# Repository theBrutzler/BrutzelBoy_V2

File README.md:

https://github.com/jsc69/theLittleBrutzelboy/releases/tag/0.8a
link to the brutzleboy game

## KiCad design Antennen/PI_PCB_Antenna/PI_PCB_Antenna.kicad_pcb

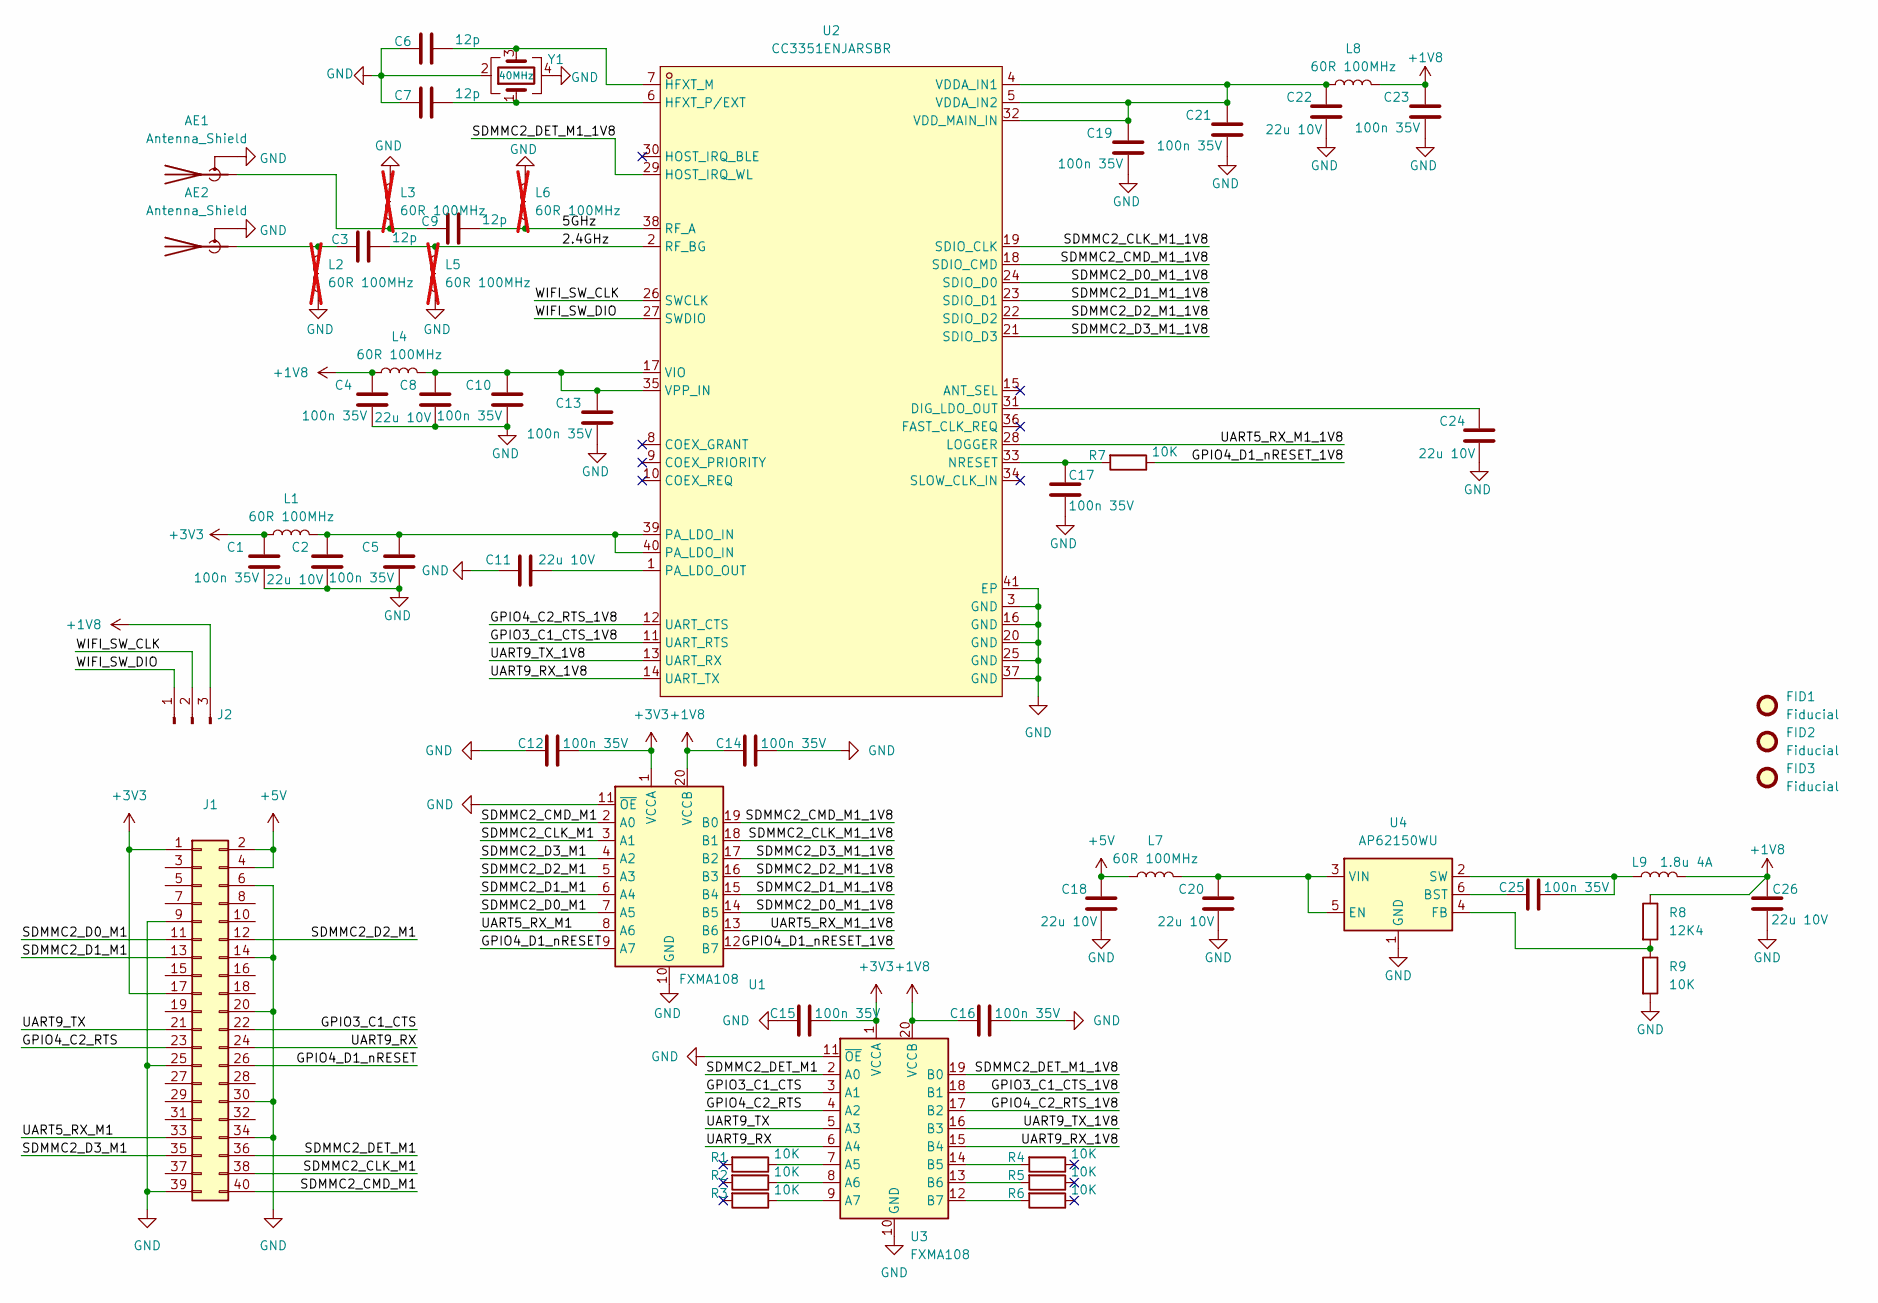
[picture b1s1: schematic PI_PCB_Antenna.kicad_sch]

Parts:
AE1, AE2: Antenna_Shield; PI_Antenne
C1, C4, C5, C10, C12, C13, C14, C15, C16, C17, C19, C21, C23, C25: 100n 35V; C_0603_1608Metric; LCSC C48579281
C2, C8, C11, C18, C20, C22, C24, C26: 22u 10V; C_0603_1608Metric; LCSC C7432770
C3, C6, C7, C9: 12p; C_0603_1608Metric; LCSC C45359931
FID1, FID2, FID3: Fiducial; Fiducial_0.5mm_Mask1mm
J1: Conn_02x20_Odd_Even; PinHeader_2x20_P2.54mm_Vertical
J2: Conn_01x03_Pin; PinHeader_1x03_P2.54mm_Vertical
L1, L4, L7, L8: 60R 100MHz; L_0603_1608Metric; LCSC C356980
L2, L3, L5, L6: 60R 100MHz; L_0603_1608Metric; LCSC C356980; not fitted
L9: 1.8u 4A; L_1008_2520Metric; LCSC C53285288
R1, R2, R3, R4, R5, R6, R7, R9: 10K; R_0603_1608Metric
R8: 12K4; R_0603_1608Metric
U1, U3: FXMA108; WQFN-20-1EP_2.5x4.5mm_P0.5mm_EP1x2.9mm
U2: CC3351ENJARSBR; WQFN-40_L5.0-W5.0-P0.40-TL-EP3.5; LCSC Part C41671458
U4: AP62150WU; TSOT-23-6; LCSC C3194237
Y1: 40MHz; Oscillator_SMD_ECS_2520MV-xxx-xx-4Pin_2.5x2.0mm; LCSC C337601

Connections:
+1V8: C4.1, C14.1, C16.1, C23.1, C26.2, J2.3, L4.1, L8.2, L9.2, R8.1, U1.20 (VCCB), U3.20 (VCCB)
+3V3: C1.1, C12.2, C15.2, J1.1, J1.17, L1.1, U1.1 (VCCA), U3.1 (VCCA)
+5V: C18.2, J1.2, J1.4, L7.1
/2.4GHz: C3.2, L5.2, U2.2 (RF_BG)
/5GHz: C9.2, L6.1, U2.38 (RF_A)
/GPIO3_C1_CTS: J1.22, U3.3 (A1)
/GPIO3_C1_CTS_1V8: U2.11 (UART_RTS), U3.18 (B1)
/GPIO4_C2_RTS: J1.23, U3.4 (A2)
/GPIO4_C2_RTS_1V8: U2.12 (UART_CTS), U3.17 (B2)
/GPIO4_D1_nRESET: J1.26, U1.9 (A7)
/GPIO4_D1_nRESET_1V8: R7.1, U1.12 (B7)
/SDMMC2_CLK_M1: J1.38, U1.3 (A1)
/SDMMC2_CLK_M1_1V8: U1.18 (B1), U2.19 (SDIO_CLK)
/SDMMC2_CMD_M1: J1.40, U1.2 (A0)
/SDMMC2_CMD_M1_1V8: U1.19 (B0), U2.18 (SDIO_CMD)
/SDMMC2_D0_M1: J1.11, U1.7 (A5)
/SDMMC2_D0_M1_1V8: U1.14 (B5), U2.24 (SDIO_D0)
/SDMMC2_D1_M1: J1.13, U1.6 (A4)
/SDMMC2_D1_M1_1V8: U1.15 (B4), U2.23 (SDIO_D1)
/SDMMC2_D2_M1: J1.12, U1.5 (A3)
/SDMMC2_D2_M1_1V8: U1.16 (B3), U2.22 (SDIO_D2)
/SDMMC2_D3_M1: J1.35, U1.4 (A2)
/SDMMC2_D3_M1_1V8: U1.17 (B2), U2.21 (SDIO_D3)
/SDMMC2_DET_M1: J1.36, U3.2 (A0)
/SDMMC2_DET_M1_1V8: U2.29 (HOST_IRQ_WL), U3.19 (B0)
/UART5_RX_M1: J1.33, U1.8 (A6)
/UART5_RX_M1_1V8: U1.13 (B6), U2.28 (LOGGER)
/UART9_RX: J1.24, U3.6 (A4)
/UART9_RX_1V8: U2.14 (UART_TX), U3.15 (B4)
/UART9_TX: J1.21, U3.5 (A3)
/UART9_TX_1V8: U2.13 (UART_RX), U3.16 (B3)
/WIFI_SW_CLK: J2.2, U2.26 (SWCLK)
/WIFI_SW_DIO: J2.1, U2.27 (SWDIO)
GND: AE1.2 (Shield), AE2.2 (Shield), C1.2, C2.1, C4.2, C5.2, C6.1, C7.1, C8.1, C10.2, C11.1, C12.1, C13.2, C14.2, C15.1, C16.2, C17.2, C18.1, C19.2, C20.1, C21.2, C22.1, C23.2, C24.1, C26.1, J1.6, J1.9, J1.14, J1.20, J1.25, J1.30, J1.34, J1.39, L2.1, L3.2, L5.1, L6.2, R9.2, U1.10 (GND), U1.11 (~OE), U2.3 (GND), U2.16 (GND), U2.20 (GND), U2.25 (GND), U2.37 (GND), U2.41 (EP), U3.10 (GND), U3.11 (~OE), U4.1 (GND), Y1.2, Y1.4
unnamed: AE1.1 (A), C9.1, L3.1
unnamed: AE2.1 (A), C3.1, L2.2
unnamed: C2.2, C5.1, L1.2, U2.39 (PA_LDO_IN), U2.40 (PA_LDO_IN)
unnamed: C24.2, U2.31 (DIG_LDO_OUT)
unnamed: C6.2, U2.7 (HFXT_M), Y1.3
unnamed: C7.2, U2.6 (HFXT_P/EXT), Y1.1
unnamed: C17.1, R7.2, U2.33 (NRESET)
unnamed: C11.2, U2.1 (PA_LDO_OUT)
unnamed: C19.1, C21.1, C22.2, L8.1, U2.4 (VDDA_IN1), U2.5 (VDDA_IN2), U2.32 (VDD_MAIN_IN)
unnamed: C8.2, C10.1, C13.1, L4.2, U2.17 (VIO), U2.35 (VPP_IN)
unnamed: R1.1, U3.7 (A5)
unnamed: R2.1, U3.8 (A6)
unnamed: R3.1, U3.9 (A7)
unnamed: R4.2, U3.14 (B5)
unnamed: R5.2, U3.13 (B6)
unnamed: R6.2, U3.12 (B7)
unnamed: C25.1, U4.6 (BST)
unnamed: C20.2, L7.2, U4.3 (VIN), U4.5 (EN)
unnamed: R8.2, R9.1, U4.4 (FB)
unnamed: C25.2, L9.1, U4.2 (SW)

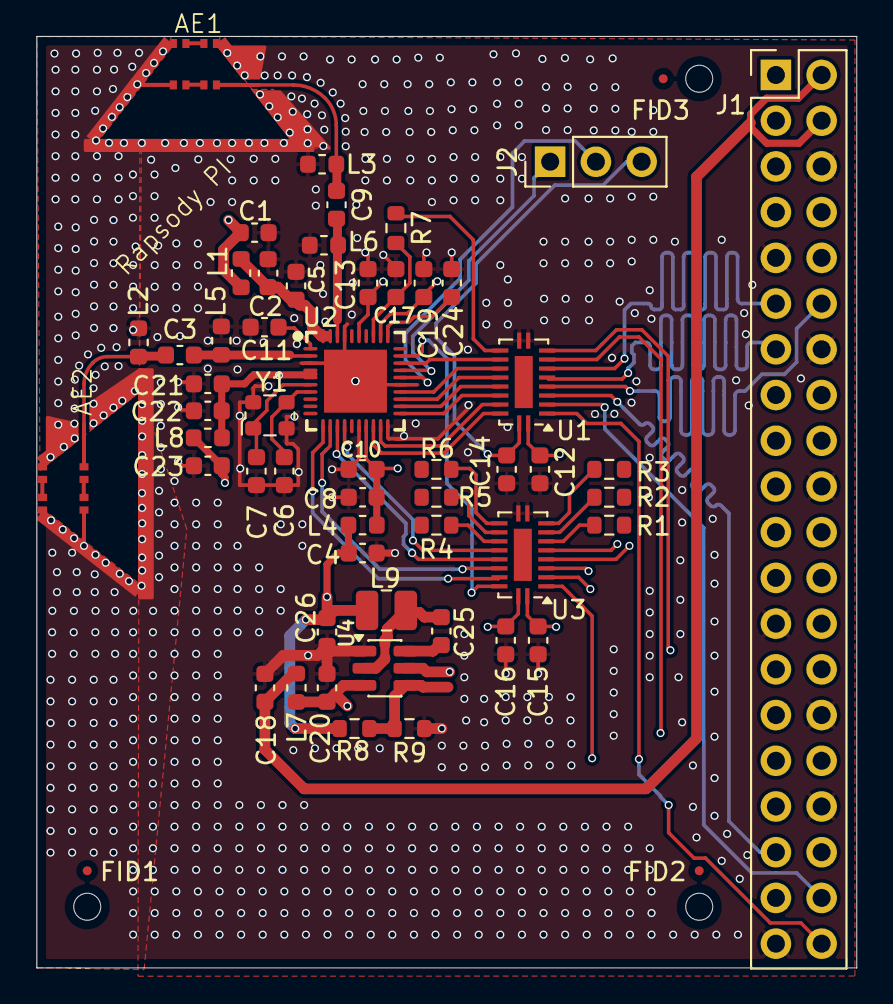
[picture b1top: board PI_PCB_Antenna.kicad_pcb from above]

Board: 4 copper layers, 45.6 x 51.8 mm, 56 parts (0 on the bottom side), 54 nets.

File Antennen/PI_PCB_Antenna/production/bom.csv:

Designator,Footprint,Quantity,Value,LCSC Part #
"AE1, AE2",PI_Antenne,2,Antenna_Shield,
"C1, C10, C12, C13, C14, C15, C16, C17, C19, C21, C23, C25, C4, C5",0603,14,100n 35V,C48579281
"C11, C18, C2, C20, C22, C24, C26, C8",0603,8,22u 10V,C7432770
"C3, C6, C7, C9",0603,4,12p,C45359931
J1,PinHeader_2x20_P2.54mm_Vertical,1,Conn_02x20_Odd_Even,
J2,PinHeader_1x03_P2.54mm_Vertical,1,Conn_01x03_Pin,
"L1, L4, L7, L8",0603,4,60R 100MHz,C356980
L9,1008,1,1.8u 4A,C53285288
"R1, R2, R3, R4, R5, R6, R7, R9",0603,8,10K,
R8,0603,1,12K4,
"U1, U3",WQFN-20-1EP_2.5x4.5mm_P0.5mm_EP1x2.9mm,2,FXMA108,
U2,WQFN-40_L5.0-W5.0-P0.40-TL-EP3.5,1,CC3351ENJARSBR,C41671458
U4,TSOT-23-6,1,AP62150WU,C3194237
Y1,Oscillator_SMD_ECS_2520MV-xxx-xx-4Pin_2.5x2.0mm,1,40MHz,C337601

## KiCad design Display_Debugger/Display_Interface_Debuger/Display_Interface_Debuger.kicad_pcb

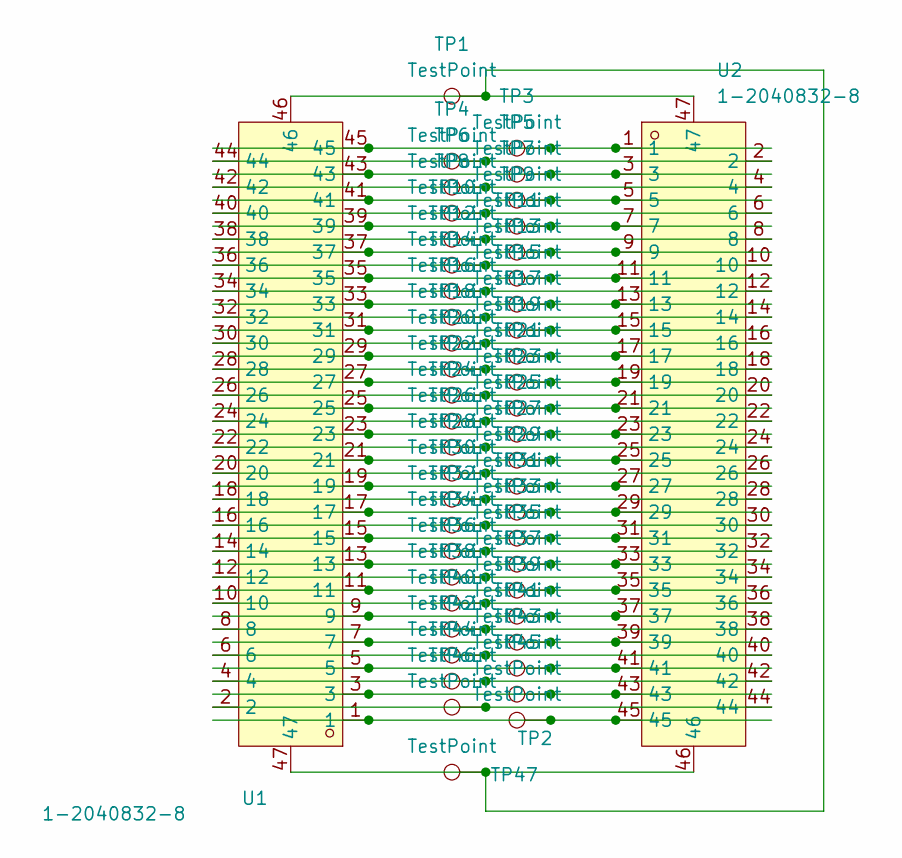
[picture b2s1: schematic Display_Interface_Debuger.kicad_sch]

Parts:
TP1, TP47: TestPoint; TestPoint_Loop_D2.50mm_Drill1.0mm
TP2, TP3, TP4, TP5, TP6, TP7, TP8, TP9, TP10, TP11, TP12, TP13, TP14, TP15, TP16, TP17, TP18, TP19, TP20, TP21, TP22, TP23, TP24, TP25, TP26, TP27, TP28, TP29, TP30, TP31, TP32, TP33, TP34, TP35, TP36, TP37, TP38, TP39, TP40, TP41, TP42, TP43, TP44, TP45, TP46: TestPoint; TestPoint_Pad_D0.7mm_without_spacing
U1, U2: 1-2040832-8; FPC-SMD_45P-P0.50; LCSC Part C19078618

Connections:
unnamed: TP1.1, TP47.1, U1.46, U1.47, U2.46, U2.47
unnamed: TP2.1, U1.1, U2.45
unnamed: TP3.1, U1.45, U2.1
unnamed: TP4.1, U1.44, U2.2
unnamed: TP5.1, U1.43, U2.3
unnamed: TP6.1, U1.42, U2.4
unnamed: TP7.1, U1.41, U2.5
unnamed: TP8.1, U1.40, U2.6
unnamed: TP9.1, U1.39, U2.7
unnamed: TP10.1, U1.38, U2.8
unnamed: TP11.1, U1.37, U2.9
unnamed: TP12.1, U1.36, U2.10
unnamed: TP13.1, U1.35, U2.11
unnamed: TP14.1, U1.34, U2.12
unnamed: TP15.1, U1.33, U2.13
unnamed: TP16.1, U1.32, U2.14
unnamed: TP17.1, U1.31, U2.15
unnamed: TP18.1, U1.30, U2.16
unnamed: TP19.1, U1.29, U2.17
unnamed: TP20.1, U1.28, U2.18
unnamed: TP21.1, U1.27, U2.19
unnamed: TP22.1, U1.26, U2.20
unnamed: TP23.1, U1.25, U2.21
unnamed: TP24.1, U1.24, U2.22
unnamed: TP25.1, U1.23, U2.23
unnamed: TP26.1, U1.22, U2.24
unnamed: TP27.1, U1.21, U2.25
unnamed: TP28.1, U1.20, U2.26
unnamed: TP29.1, U1.19, U2.27
unnamed: TP30.1, U1.18, U2.28
unnamed: TP31.1, U1.17, U2.29
unnamed: TP32.1, U1.16, U2.30
unnamed: TP33.1, U1.15, U2.31
unnamed: TP34.1, U1.14, U2.32
unnamed: TP35.1, U1.13, U2.33
unnamed: TP36.1, U1.12, U2.34
unnamed: TP37.1, U1.11, U2.35
unnamed: TP38.1, U1.10, U2.36
unnamed: TP39.1, U1.9, U2.37
unnamed: TP40.1, U1.8, U2.38
unnamed: TP41.1, U1.7, U2.39
unnamed: TP42.1, U1.6, U2.40
unnamed: TP43.1, U1.5, U2.41
unnamed: TP44.1, U1.4, U2.42
unnamed: TP45.1, U1.3, U2.43
unnamed: TP46.1, U1.2, U2.44

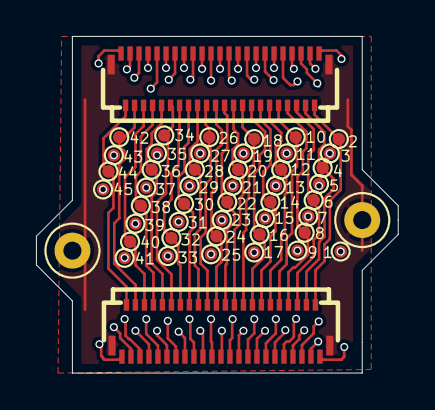
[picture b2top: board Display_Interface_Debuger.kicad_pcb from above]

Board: 4 copper layers, 20.1 x 18.7 mm, 50 parts (1 on the bottom side), 46 nets.

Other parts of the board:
SM3: SYM_Arrow45_Tiny; Symbol_kurzschlussblog

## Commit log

2025-12-21 inital upload
2025-12-21 add action to generate files automatically
2025-12-30 updat 3d models
2026-03-04 Update additional PCBs
    Add WIFI PCB to get best antenna
    Add Display Debbugger to get interface pinout
2026-05-26 Add link to brutzleboy game release
